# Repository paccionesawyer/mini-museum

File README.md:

# Mini - Museum

A voice activated rotating museum. While the options are admittedly limited, this mini museum boasts two of the most famous paintings in the world, printed on the finest white printer paper. Simply ask to see one of the two paintings, either the Mona Lisa or The Scream. One raspberry pi, the client, will take input from a microphone, parse that into text and look for a related keyword. Once it recognizes a keyword related to either painting, it will send a request to the IP Address of a second Raspberry Pi, the server, that describes which painting was mentioned. The server pi will take that information and turn a planetary gear system either 90 degrees to the right or left to display one painting on the front window and then return.

[Full Video](https://youtu.be/GzdikGhd4Ek)
## Getting Started

These instructions will get you a copy of the project up and running on your local machine for development and testing purposes.

### Prerequisites

- Client Python Libraries
  - [Speech Recognition](https://pypi.org/project/SpeechRecognition/) (Used to recognize speech on client)
    - [pyaudio](https://pypi.org/project/PyAudio/) (Dependency of Speech Recognition)
  - [requests](https://pypi.org/project/requests/) (To Send Information to the Server Pi)
- Server Python Libraries
  - [RPi.GPIO](https://pypi.org/project/RPi.GPIO/) (To Communicate with Stepper Motor)
  - [Flask](https://pypi.org/project/Flask/) (To read requests from the Client Pi)
- Equipment 
  - [NEMA-17 Stepper Motor](https://www.adafruit.com/product/324) (Actuator)
    - Stepper Motor Driver
  - [Microphone](https://www.amazon.com/Lavalier-Microphone-Cardioid-Condenser-Computer/dp/B077VNGVL2/ref=sxts_sxwds-bia-wc-rsf1_0?cv_ct_cx=microphone&dchild=1&keywords=microphone&pd_rd_i=B077VNGVL2&pd_rd_r=fd342589-1272-420f-8874-4adbbfceab7e&pd_rd_w=C1Nme&pd_rd_wg=MZaFY&pf_rd_p=5168df84-062d-4bdf-8a6e-2680813bd42f&pf_rd_r=HCAYV23MEAB58FWD417P&psc=1&qid=1613717362&sr=1-1-7bf78e84-8ef2-4f13-9926-bee5153e81cb) (Sensor)
- [Raspberry Pi 4](https://www.google.com/search?q=raspberry+pi+4&sxsrf=ALeKk03vsMgGCu7PQVxu5BVM5yzeNxULQw:1613717510216&source=lnms&tbm=shop&sa=X&ved=2ahUKEwjM7dqXrvXuAhWYWc0KHdwgBTIQ_AUoAXoECAUQAw&biw=958&bih=1087) x2
- Breadboard power supply (Accepts power from a 2.1 x 5.5 mm plug from a 12 V wall adapter. Emits 12 V, 5 V, and 3.3 V at the same time.) Custom PCB

### Installing

Simply download the files in this repository and upload the client.py code to one Raspberry Pi attached to the microphone, and the server.py code to another Raspberry Pi attached to the Stepper Motor.

### Setup Notes

In our design there was a lower box that housed the electronics, the upper box housed the gears and paintings.

## Authors

- **Sawyer Bailey Paccione** - *Client Code and Gear Design* - [Portfolio](http://sawyerbaileypaccione.tech/)
- **Olif Hordofa** - *Server Code and Box Design* 

## License

This project is licensed under the MIT License - see the [LICENSE.md](LICENSE.md) file for details

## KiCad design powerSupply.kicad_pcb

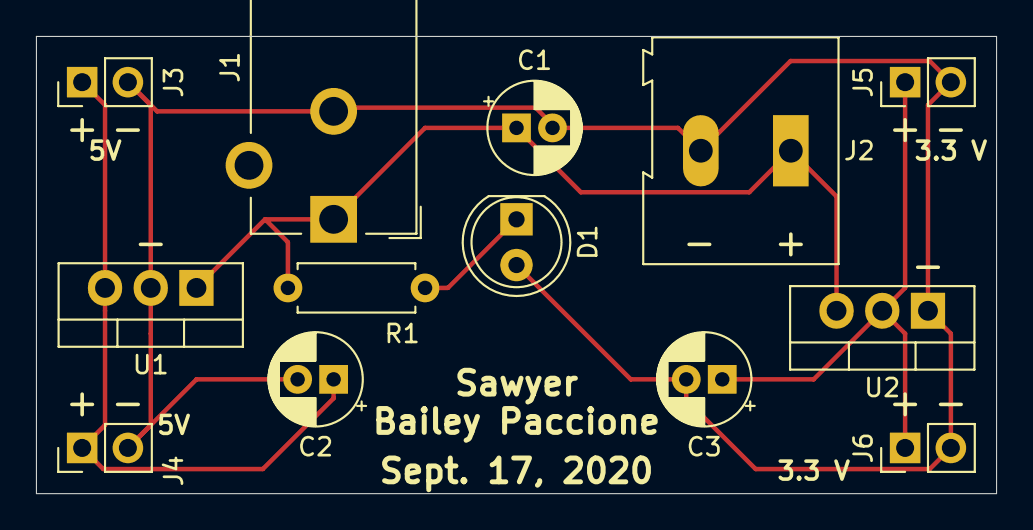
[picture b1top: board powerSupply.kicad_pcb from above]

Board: 2 copper layers, 53.3 x 25.4 mm, 13 parts (0 on the bottom side), 5 nets.

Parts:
C1, C2, C3: 10 uF; CP_Radial_D5.0mm_P2.00mm
D1: LED; LED_D5.0mm
J1: Barrel_Jack_Switch; BarrelJack_CUI_PJ-102AH_Horizontal
J2: Screw_Terminal_01x02; TerminalBlock_Altech_AK300-2_P5.00mm
J3, J4, J5, J6: Conn_01x02_Male; PinHeader_1x02_P2.54mm_Vertical
R1: R; R_Axial_DIN0207_L6.3mm_D2.5mm_P7.62mm_Horizontal
U1: L7805; TO-220-3_Vertical
U2: LD1117S33TR_SOT223; TO-220-3_Vertical

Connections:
GND: C1.2, C2.2, C3.2, D1.2, J1.2, J2.2, J3.2, J4.2, J5.2, J6.2, U1.2, U2.1
unnamed: C1.1, J1.1, J2.1, R1.1, U1.1, U2.3
unnamed: C2.1, J3.1, J4.1, U1.3
unnamed: C3.1, J5.1, J6.1, U2.2
unnamed: D1.1, R1.2
